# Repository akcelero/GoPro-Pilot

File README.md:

# GoPro-Pilot
Open source pilot for gopro hero 4 based on unofficial http api.

# READ IT BEFORE START

There is no connection between pin CH_PD and Vcc!
You need to put small wire to connect these two pins.

## Prepare board

TODO: describe how to prepare own PCB board

## Instalation

1. Put micropython into ESP<br />
`esptool.py --port /dev/ttyUSB0 --baud 460800 write_flash --flash_size=detect 0 LATEST_MICROPYTHON.bin`
2. Put credentials and main program<br />
`ampy --port /dev/ttyUSB0 put main.py /main.py`<br />
`ampy --port /dev/ttyUSB0 put credentials.config /credentials.config`
3. If pilot does not work, pls check debug output<br />
`screen /dev/ttyUSB0 115200`

## Sources:

1. List of instructions in api (congrats for this project)<br />
https://github.com/KonradIT/goprowifihack/blob/master/HERO4/WifiCommands.md
2. Micropython<br />
http://micropython.org/download#esp8266
3. Tutorial for micropython in ESP8266<br />
https://docs.micropython.org/en/latest/esp8266/esp8266/tutorial/intro.html

## License
Apache License 2.0v

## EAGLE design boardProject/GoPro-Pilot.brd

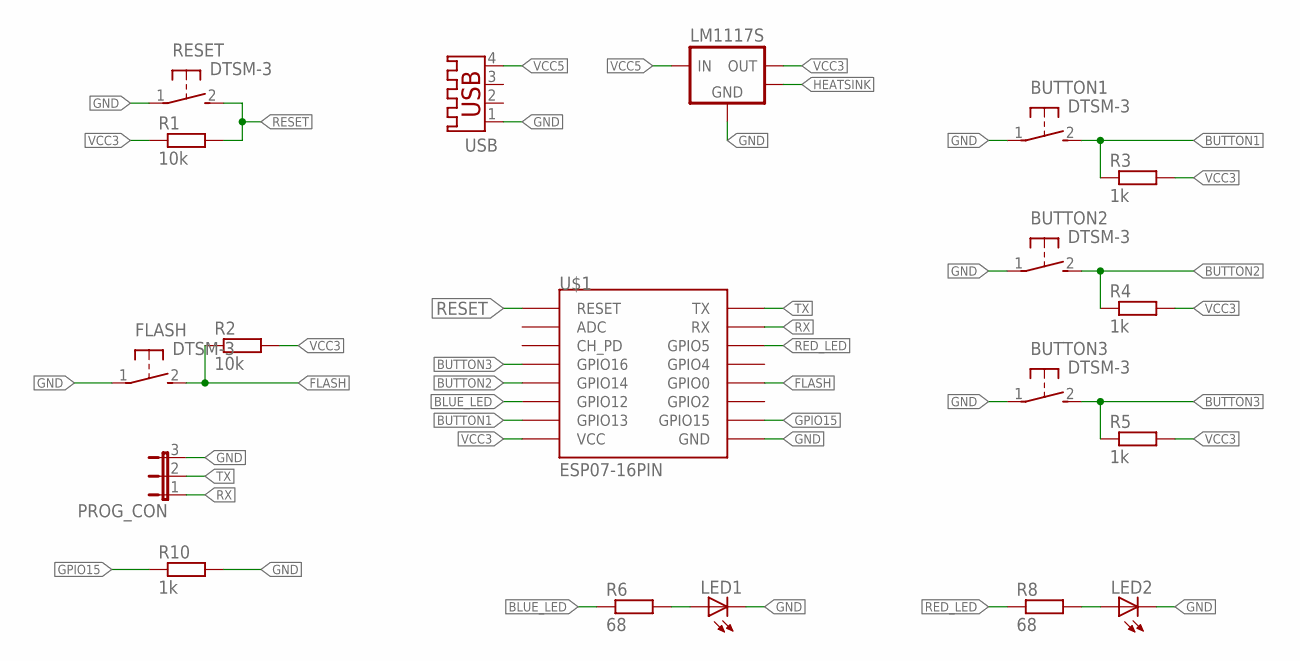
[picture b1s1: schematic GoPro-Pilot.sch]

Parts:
BUTTON1, BUTTON2, BUTTON3: DTSM-3
FLASH: DTSM-3
LED1, LED2: LEDSML0805; SML0805
LM1117S: LM1117-SOT223; SOT-223-3
PROG_CON: JP2E; JP2
R1, R2: 10k; R1005
R3, R4, R5, R10: 1k; R1005
R6, R8: 68; R1005
RESET: DTSM-3
U$1: ESP07-16PIN
USB: USB-A003

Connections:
BLUE_LED: R6.1, U$1.GPIO12
BUTTON1: BUTTON1.2, R3.1, U$1.GPIO13
BUTTON2: BUTTON2.2, R4.1, U$1.GPIO14
BUTTON3: BUTTON3.2, R5.1, U$1.GPIO16
FLASH: FLASH.2, R2.1, U$1.GPIO0
GND: BUTTON1.1, BUTTON2.1, BUTTON3.1, FLASH.1, LED1.C, LED2.C, LM1117S.1 (GND), PROG_CON.3, R10.2, RESET.1, U$1.GND, USB.1
GPIO15: R10.1, U$1.GPIO15
HEATSINK: LM1117S.4 (HEATSINK)
unnamed: LED2.A, R8.2
unnamed: LED1.A, R6.2
RED_LED: R8.1, U$1.GPIO4 (GPIO5)
RESET: R1.2, RESET.2, U$1.REST (RESET)
RX: PROG_CON.1, U$1.RX
TX: PROG_CON.2, U$1.TX
VCC3: LM1117S.2 (VOUT), R1.1, R2.2, R3.2, R4.2, R5.2, U$1.VCC
VCC5: LM1117S.3 (VIN), USB.4

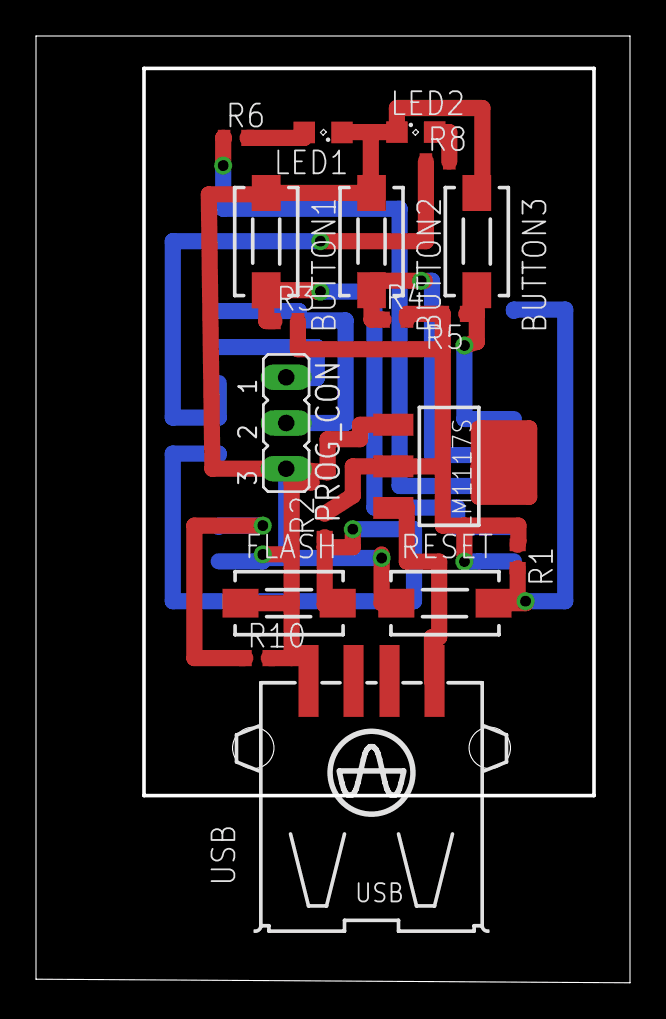
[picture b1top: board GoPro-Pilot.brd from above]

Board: 2 copper layers, 32.8 x 52.4 mm, 19 parts (1 on the bottom side), 15 nets.

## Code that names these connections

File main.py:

import network
import socket
import json
import sys
from machine import Pin
from time import sleep

network.WLAN(network.AP_IF).active(False)
network.WLAN(network.STA_IF).active(False)

try:
    with open('credentials.config') as f:
        credentials = [line.replace('\n', '') for line in f.readlines()]
except:
    print('Can not open file with credentials')
    raise

if len(credentials) != 2:
    print('Wrong struct of credentials file, check example')
    raise Error()

essid = credentials[0]
password = credentials[1]

goproIP = '10.5.5.9'

shutterPath = '/gp/gpControl/command/shutter?p=1'
stopPath = '/gp/gpControl/command/shutter?p=0'
photoMode = '/gp/gpControl/command/mode?p=1'
videoMode = '/gp/gpControl/command/mode?p=0'
locateOn = '/gp/gpControl/command/system/locate?p=1'
locateOff = '/gp/gpControl/command/system/locate?p=0'
statusPath = '/gp/gpControl/status'

blue_led = Pin(12, Pin.OUT)
red_led = Pin(4, Pin.OUT)

button1 = Pin(13, Pin.IN)
button2 = Pin(14, Pin.IN)
button3 = Pin(16, Pin.IN)

blue_led.value(0)
red_led.value(0)


def action(path):
    soc = socket.socket()
    soc.connect((goproIP, 80))
    soc.send(
            b'GET ' + path + ' HTTP/1.0\r\nHost: ' + path + '\r\n\r\n'
    )
    data = soc.read()
    soc.close()
    return data


def toggle(pin):
    pin.value(not pin.value())


def turnOn(led):
    led.value(1)


def turnOff(led):
    led.value(0)


def button1Callback(trigger):
    turnOn(blue_led)
    action(photoMode)
    action(shutterPath)
    sleep(0.2)
    turnOff(blue_led)


def button2Callback(trigger):
    turnOn(blue_led)
    data = action(statusPath)
    capturing = json.loads(
        '{' + data.decode('utf-8').split('{', 1)[1].replace('\n', '')
    )['status']['8']
    if not capturing:
        action(videoMode)
    path = '/gp/gpControl/command/shutter?p=' + str(capturing ^ 1)
    action(path)
    turnOff(blue_led)


def button3Callback(trigger):
    turnOn(blue_led)
    data = action(statusPath)
    locate = json.loads(
        '{' + data.decode('utf-8').split('{', 1)[1].replace('\n', '')
    )['status']['45']
    path = '/gp/gpControl/command/system/locate?p=' + str(locate ^ 1)
    action(path)
    turnOff(blue_led)


# ------- Initialize connect with camera -----------

sta = network.WLAN(network.STA_IF)
sta.active(True)
sta.connect(essid, password)

# ---- Inform about trying connect with camera -----

while not sta.isconnected():
    toggle(red_led)
    sleep(0.5)
turnOff(red_led)

# ------- Inform about succesful connection ---------

for i in range(8):
    toggle(blue_led)
    sleep(0.2)

# -------- Setup interrupts on buttons pins ----------

button1.irq(trigger=Pin.IRQ_FALLING, handler=button1Callback)
button2.irq(trigger=Pin.IRQ_FALLING, handler=button2Callback)
# GPIO16 has no IRQ function
# button3.irq(trigger=Pin.IRQ_FALLING, handler=button2Callback)

# Simulate callback at falling edge at button nr 3
prevStatusButton3 = button3.value()
while True:
    if prevStatusButton3 == 0 and not (prevStatusButton3 == button3.value()):
        button3Callback(button3)
    prevStatusButton3 = button3.value()
    sleep(0.2)

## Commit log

2017-10-05 Initial
2017-10-05 add board project
